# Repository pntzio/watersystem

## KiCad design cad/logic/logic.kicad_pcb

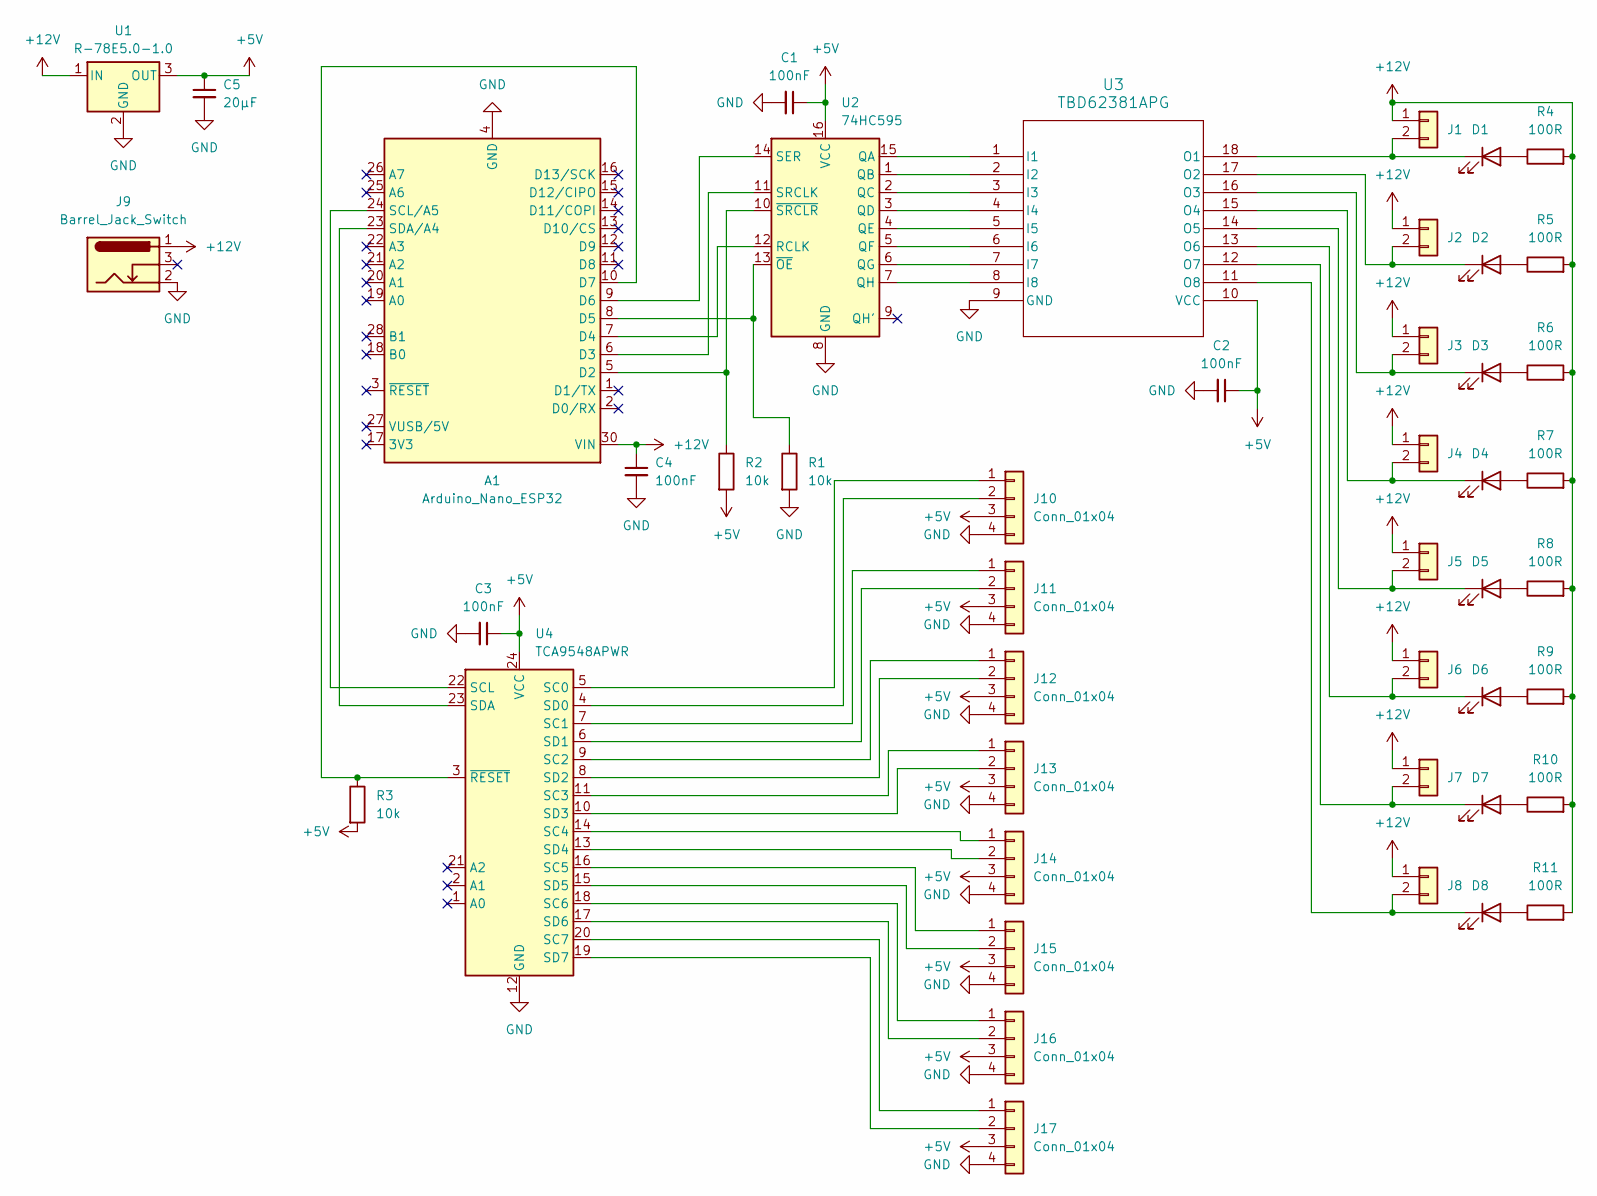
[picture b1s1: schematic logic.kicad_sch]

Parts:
A1: Arduino_Nano_ESP32; Arduino_Nano
C1, C2, C3, C4: 100nF; C_Disc_D4.7mm_W2.5mm_P5.00mm
C5: 20µF; C_Disc_D4.7mm_W2.5mm_P5.00mm
D1, D2, D3, D4, D5, D6, D7, D8: LED; LED_D3.0mm
J1, J2, J3, J4, J5, J6, J7, J8: Conn_01x02; JST_PH_B2B-PH-K_1x02_P2.00mm_Vertical
J9: Barrel_Jack_Switch; BarrelJack_Horizontal
J10, J11, J12, J13, J14, J15, J16, J17: Conn_01x04; JST_PH_B4B-PH-K_1x04_P2.00mm_Vertical
R1, R2, R3: 10k; R_Axial_DIN0207_L6.3mm_D2.5mm_P7.62mm_Horizontal
R4, R5, R6, R7, R8, R9, R10, R11: 100R; R_Axial_DIN0207_L6.3mm_D2.5mm_P7.62mm_Horizontal
U1: R-78E5.0-1.0; Converter_DCDC_RECOM_R-78E-0.5_THT
U2: 74HC595; DIP-16_W7.62mm_Socket
U3: TBD62381APG; CERDIP-18_W7.62mm_SideBrazed_Socket
U4: TCA9548APWR; DIP-24_18.0mmx34.29mm_W15.24mm_Socket

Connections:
+5V: C1.1, C2.1, C3.1, C5.1, J10.3, J11.3, J12.3, J13.3, J14.3, J15.3, J16.3, J17.3, R2.2, R3.2, U1.3 (OUT), U2.16 (VCC), U3.10 (VCC), U4.24 (VCC)
+12V: A1.30 (VIN), C4.1, J1.1, J2.1, J3.1, J4.1, J5.1, J6.1, J7.1, J8.1, J9.1, R4.2, R5.2, R6.2, R7.2, R8.2, R9.2, R10.2, R11.2, U1.1 (IN)
GND: A1.4 (GND), A1.29 (GND), C1.2, C2.2, C3.2, C4.2, C5.2, J9.2, J10.4, J11.4, J12.4, J13.4, J14.4, J15.4, J16.4, J17.4, R1.2, U1.2 (GND), U2.8 (GND), U3.9 (GND), U4.12 (GND)
unnamed: A1.5 (D2), R2.1, U2.10 (~SRCLR)
unnamed: A1.6 (D3), U2.11 (SRCLK)
unnamed: A1.7 (D4), U2.12 (RCLK)
unnamed: A1.8 (D5), R1.1, U2.13 (~OE)
unnamed: A1.9 (D6), U2.14 (SER)
unnamed: A1.10 (D7), R3.1, U4.3 (~RESET)
unnamed: A1.24 (SCL/A5), U4.22 (SCL)
unnamed: A1.23 (SDA/A4), U4.23 (SDA)
unnamed: D1.2 (A), R4.1
unnamed: D1.1 (K), J1.2, U3.18 (O1)
unnamed: D2.2 (A), R5.1
unnamed: D2.1 (K), J2.2, U3.17 (O2)
unnamed: D3.2 (A), R6.1
unnamed: D3.1 (K), J3.2, U3.16 (O3)
unnamed: D4.2 (A), R7.1
unnamed: D4.1 (K), J4.2, U3.15 (O4)
unnamed: D5.2 (A), R8.1
unnamed: D5.1 (K), J5.2, U3.14 (O5)
unnamed: D6.2 (A), R9.1
unnamed: D6.1 (K), J6.2, U3.13 (O6)
unnamed: D7.2 (A), R10.1
unnamed: D7.1 (K), J7.2, U3.12 (O7)
unnamed: D8.2 (A), R11.1
unnamed: D8.1 (K), J8.2, U3.11 (O8)
unnamed: J10.1, U4.5 (SC0)
unnamed: J10.2, U4.4 (SD0)
unnamed: J11.1, U4.7 (SC1)
unnamed: J11.2, U4.6 (SD1)
unnamed: J12.1, U4.9 (SC2)
unnamed: J12.2, U4.8 (SD2)
unnamed: J13.1, U4.11 (SC3)
unnamed: J13.2, U4.10 (SD3)
unnamed: J14.1, U4.14 (SC4)
unnamed: J14.2, U4.13 (SD4)
unnamed: J15.1, U4.16 (SC5)
unnamed: J15.2, U4.15 (SD5)
unnamed: J16.1, U4.18 (SC6)
unnamed: J16.2, U4.17 (SD6)
unnamed: J17.1, U4.20 (SC7)
unnamed: J17.2, U4.19 (SD7)
unnamed: U2.15 (QA), U3.1 (I1)
unnamed: U2.1 (QB), U3.2 (I2)
unnamed: U2.2 (QC), U3.3 (I3)
unnamed: U2.3 (QD), U3.4 (I4)
unnamed: U2.4 (QE), U3.5 (I5)
unnamed: U2.5 (QF), U3.6 (I6)
unnamed: U2.6 (QG), U3.7 (I7)
unnamed: U2.7 (QH), U3.8 (I8)

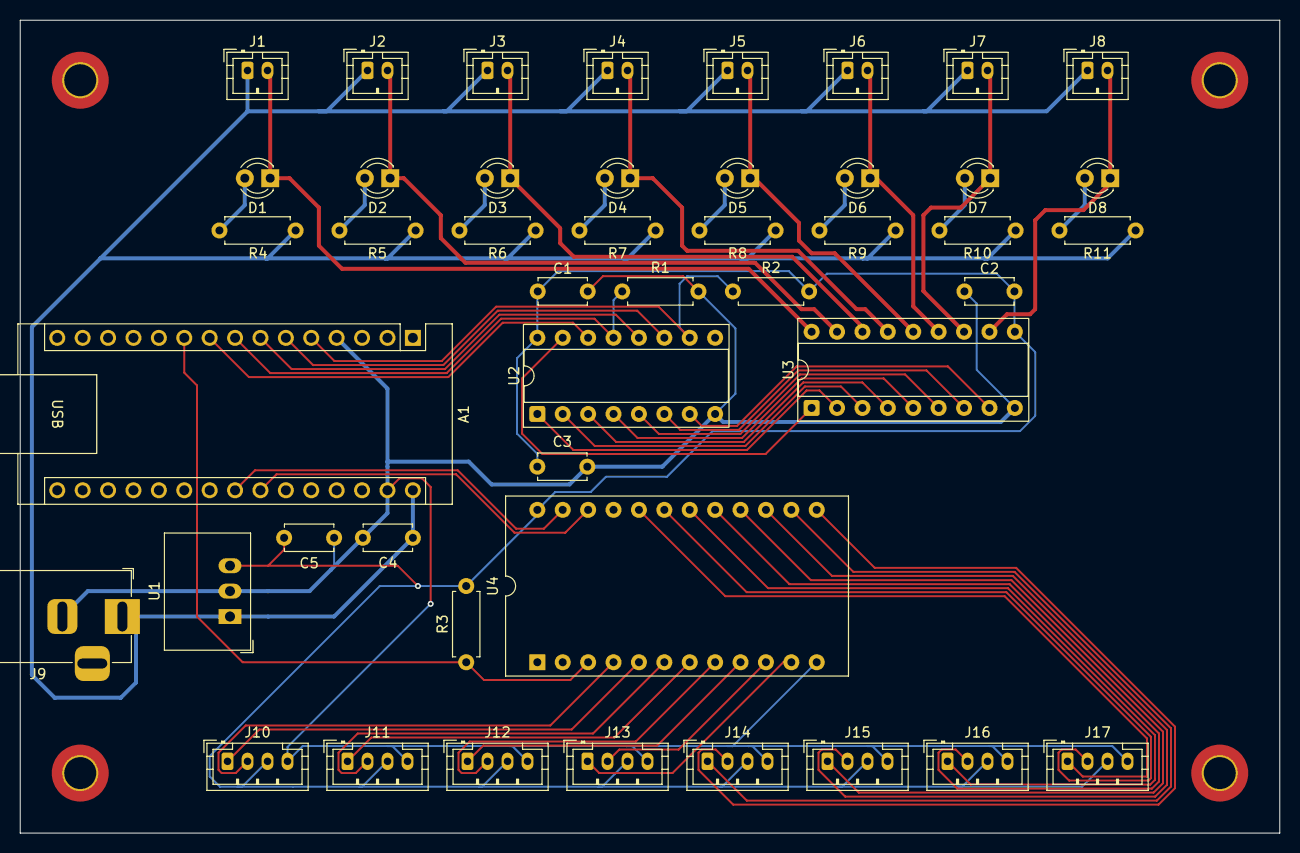
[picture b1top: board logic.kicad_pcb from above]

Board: 2 copper layers, 125.9 x 81.3 mm, 50 parts (0 on the bottom side), 51 nets.

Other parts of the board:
M1, M2, M3, M4: MountingHole_3.2mm_M3_ISO7380_Pad_TopBottom

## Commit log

2025-08-06 Inital commit
2025-08-06 Removed files not meant for VC
2025-08-06 Simplified schema and wired PCB
2025-08-15 Initial design complete
2025-08-15 Remove zipfile
2025-08-19 Added capacitor
